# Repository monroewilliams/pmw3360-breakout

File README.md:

# Notes on this fork

I created this fork of jfedor2's excellent pmw3360-breakout board because I wanted a breakout that would better serve my particular needs.

Specifically, I wanted it to fit the existing plastics of [my trackball design](https://github.com/monroewilliams/trackball), which means having roughly the same dimensions and mounting hole locations as the ones I originally sourced from MrJohnK on Tindie [here](https://www.tindie.com/products/jkicklighter/pmw3360-motion-sensor/) (that one has been discontinued, but there are similar ones available from other sellers on Tindie).

Instead of the 2.54mm pitch pin header, also I wanted it to have a JST-SH (1.0mm pitch) connector with a regularized pinout based on [Pmod type 2](https://en.wikipedia.org/wiki/Pmod_Interface) so I can easily assemble it using compact off-the-shelf cables.

Since I don't need level-shifters (I'm using it with microcontrollers that already have compatible 3.3v logic), this breakout seemed like the perfect starting point. 

Any issues with the changes I made to this layout are solely my fault, so please don't bother jfedor2 with them. :) 

Original (pre-fork) readme follows:

# PMW3360 breakout board

The board doesn't do any level shifting so it only works with 3.3V logic.

The dimensions of the board are 22x34mm and the mounting holes are for M2 screws.

The files in the [fabrication](fabrication) folder can be used to order this board from JLCPCB with SMT assembly. The board you get includes everything except the actual sensor. If some of the specific components are out of stock, try to find an equivalent with the same package and parameters.

The sensor chip should be soldered on the top side (the side where all the other components are). The dot marks pin 1. The optic goes on the bottom side.

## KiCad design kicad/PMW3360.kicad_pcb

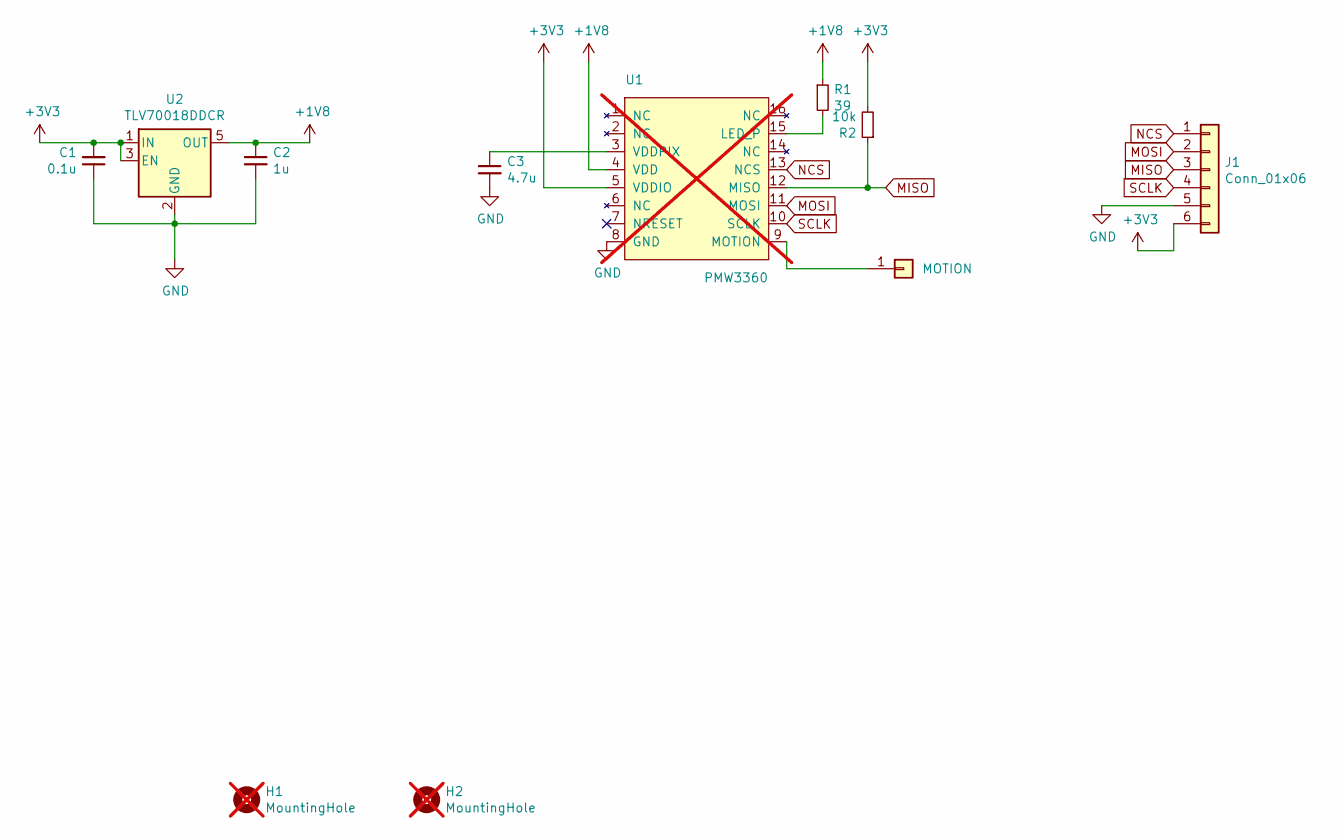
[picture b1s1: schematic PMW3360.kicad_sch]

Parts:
C1: 0.1u; C_0603_1608Metric; LCSC C14663
C2: 1u; C_0603_1608Metric; LCSC C15849
C3: 4.7u; C_0603_1608Metric; LCSC C19666
H1, H2: MountingHole; MountingHole_2.2mm_M2; not fitted
J1: Conn_01x06; JST_SH_BM06B-SRSS-TB_1x06-1MP_P1.00mm_Vertical; LCSC C7430455
J2: MOTION; PinSocket_1x01_P2.54mm_Vertical
R1: 39; R_0603_1608Metric; LCSC C137733
R2: 10k; R_0603_1608Metric; LCSC C25804
U1: PMW3360; not fitted
U2: TLV70018DDCR; SOT-23-5; LCSC C79924

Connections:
+1V8: C2.1, R1.1, U1.4 (VDD), U2.5 (OUT)
+3V3: C1.2, J1.6, R2.2, U1.5 (VDDIO), U2.1 (IN), U2.3 (EN)
GND: C1.1, C2.2, C3.2, J1.5, U1.8 (GND), U2.2 (GND)
MISO: J1.3, R2.1, U1.12 (MISO)
MOSI: J1.2, U1.11 (MOSI)
NCS: J1.1, U1.13 (NCS)
unnamed: J2.1, U1.9 (MOTION)
unnamed: R1.2, U1.15 (LED_P)
unnamed: C3.1, U1.3 (VDDPIX)
SCLK: J1.4, U1.10 (SCLK)

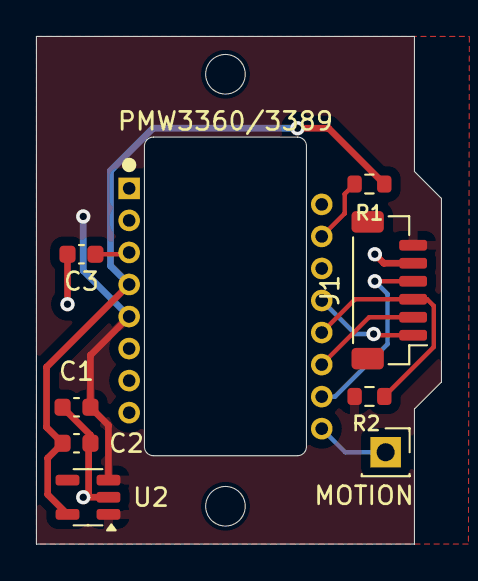
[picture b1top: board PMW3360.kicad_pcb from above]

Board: 2 copper layers, 22.5 x 28.2 mm, 11 parts (0 on the bottom side), 10 nets.

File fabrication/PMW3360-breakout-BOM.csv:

"Designator","Comment","Footprint","DNP","LCSC"
"U2","TLV70018DDCR","Package_TO_SOT_SMD:SOT-23-5","","C79924"
"R2","10k","Resistor_SMD:R_0603_1608Metric","","C25804"
"R1","39","Resistor_SMD:R_0603_1608Metric","","C137733"
"J1","Conn_01x06","PMW3360:JST_SH_BM06B-SRSS-TB_1x06-1MP_P1.00mm_Vertical","","C7430455"
"C3","4.7u","Capacitor_SMD:C_0603_1608Metric","","C19666"
"C2","1u","Capacitor_SMD:C_0603_1608Metric","","C15849"
"C1","0.1u","Capacitor_SMD:C_0603_1608Metric","","C14663"

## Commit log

2024-12-25 Modified the board dimensions and mounting hole locations to roughly match the old MrJohnK boards from Tindie (22x28mm, with two mounting holes) Changed the connector to a 6-pin JST SH 1.0mm pitch pl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
2024-12-26 Switched to JST_GH 1.25mm side-entry plug. Updated part info for the 1.8v regulator to the one that's actually available through JLCPCB.
2024-12-28 Change back to JST SH 1.0mm pitch connector Use top-side 3.3v fill zone for simpler routing add .gitignore file
2025-01-02 Update the readme for this fork. Add the url of this github repository to the rear silkscreen layer.
2025-01-16 Make more symmetrical. Clean up silkscreens a bit. Add a pad for the motion line.
